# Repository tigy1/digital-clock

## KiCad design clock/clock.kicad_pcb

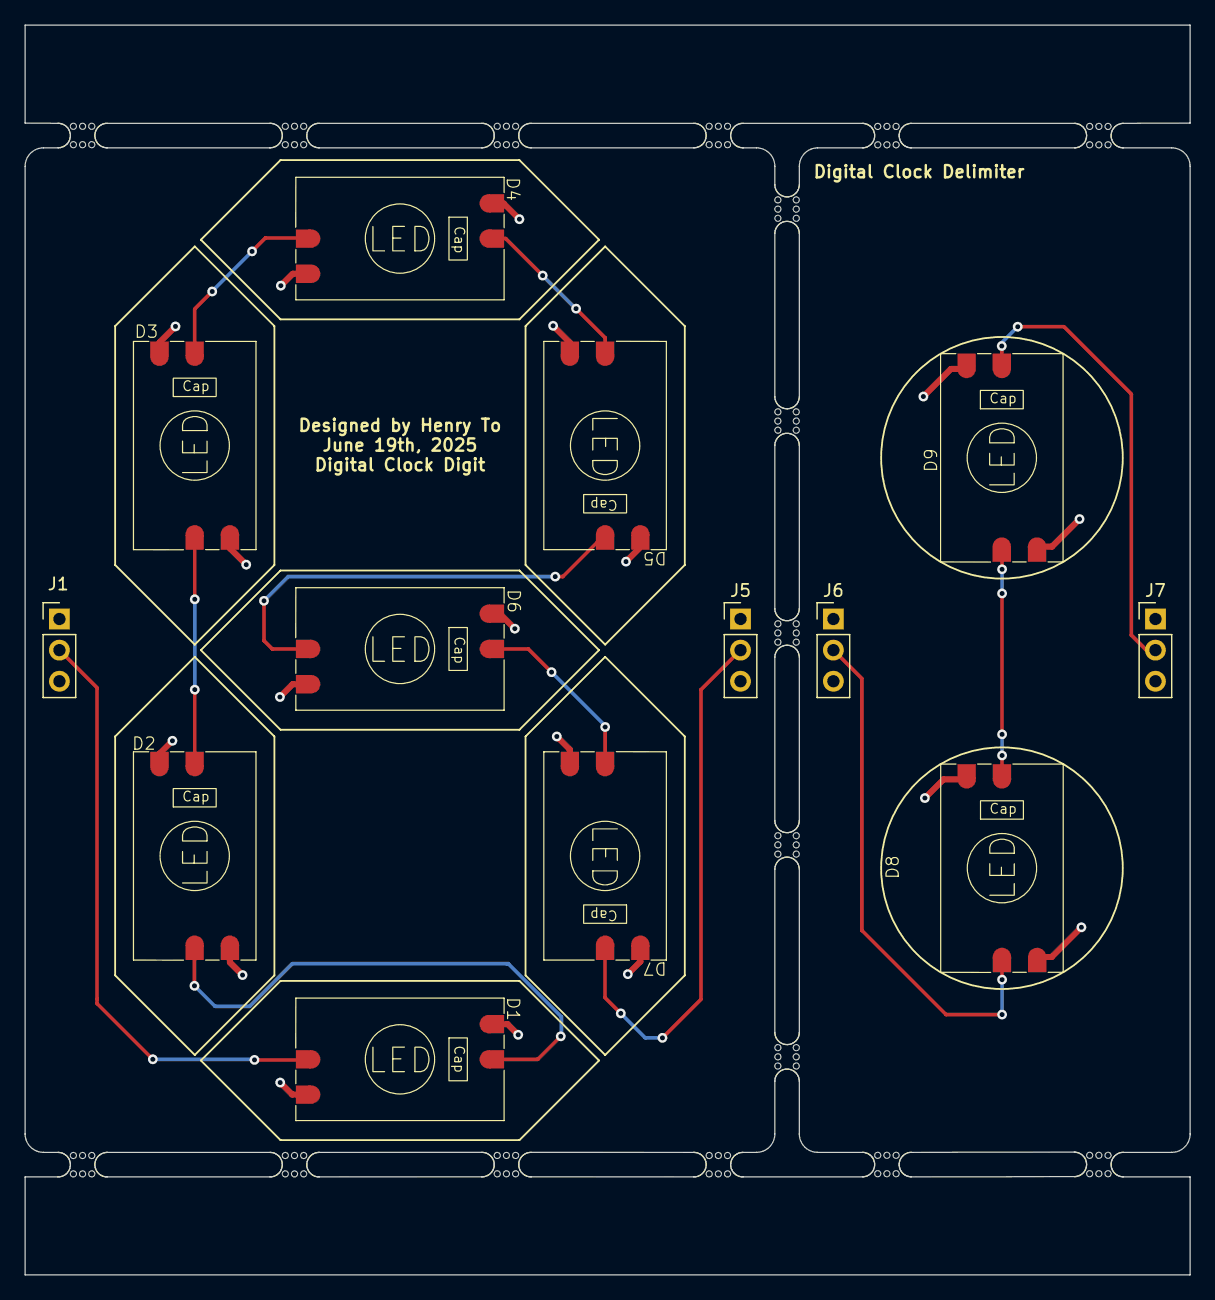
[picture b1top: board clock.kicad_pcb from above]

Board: 4 copper layers, 95.1 x 102.0 mm, 30 parts (0 on the bottom side), 14 nets.

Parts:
D1, D2, D3, D4, D5, D6, D7, D8, D9: WS2812B; oneLED
J1, J5, J6, J7: LED_connector; PinHeader_1x03_P2.54mm_Vertical
mouse-bite-2mm-slot, mouse-bite-2mm-slot1, mouse-bite-2mm-slot2, mouse-bite-2mm-slot3, mouse-bite-2mm-slot3#2, mouse-bite-2mm-slot3#3, mouse-bite-2mm-slot4, mouse-bite-2mm-slot5, mouse-bite-2mm-slot6, mouse-bite-2mm-slot7, mouse-bite-2mm-slot8, mouse-bite-2mm-slot9, mouse-bite-2mm-slot10, mouse-bite-2mm-slot11, mouse-bite-2mm-slot12, mouse-bite-2mm-slot13, mouse-bite-2mm-slot14: VAL**; mouse-bite-2mm-slot

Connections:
5V: D1.1 (VDD), D2.1 (VDD), D3.1 (VDD), D4.1 (VDD), D5.1 (VDD), D6.1 (VDD), D7.1 (VDD), J1.3, J5.3
5V2: D8.1 (VDD), D9.1 (VDD), J6.3, J7.3
D_In1: D1.4 (DIN), J1.2
D_In2: D8.4 (DIN), J6.2
D_Out1: D7.2 (DOUT), J5.2
D_Out2: D9.2 (DOUT), J7.2
GND: D1.3 (VSS), D2.3 (VSS), D3.3 (VSS), D4.3 (VSS), D5.3 (VSS), D6.3 (VSS), D7.3 (VSS), D8.3 (VSS), D9.3 (VSS), J1.1, J5.1, J6.1, J7.1
unnamed: D1.2 (DOUT), D2.4 (DIN)
unnamed: D2.2 (DOUT), D3.4 (DIN)
unnamed: D3.2 (DOUT), D4.4 (DIN)
unnamed: D4.2 (DOUT), D5.4 (DIN)
unnamed: D5.2 (DOUT), D6.4 (DIN)
unnamed: D6.2 (DOUT), D7.4 (DIN)
unnamed: D8.2 (DOUT), D9.4 (DIN)

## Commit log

2025-05-28 Added current KiCad files, almost finished LED schematic, microcontroller board & PCB design in progress
2025-05-28 Initialized stm32 code w/ stm32f103c6tx microcontroller
2025-05-30 Setup settings (UART, TIM2 timer, clock, & DMA) for microcontroller
2025-06-06 Wrote initialization functiosn for sending data to LED
    + basic preset functions for clearing all LEDS or setting all white
2025-06-06 committed changes of what previous commit message said
2025-06-06 Fixed bug where I used wrong MCU, replaced MCU & made new project file
2025-06-06 Added data sent flag and fixed up functions (dma_send & set functions)
2025-06-19 finished LED digit PCB, added gerber files, moved microcontroller kicad pcb files to different directory
2025-06-23 initialized i2c settings w/ microcontroller for ds3231
2025-06-23 prev message*
2025-06-25 created functions for ds3231 usage
    functions:
    - DS3231 register time initialization
    - Display current ds3231 time as digital leds
    - DS3231 i2c parsing
    - Decimal to DS3231 BCD conversion and vice versa
    *Also fixed function error by writing all function declarations
2025-06-26 Optimized code for size & tested code works
    - Code flash too large (>32k bits so did -Os optimization)
    - Digital clock led display based on Ds3231 works
    To Do: Make it so that digital clock is updated every minute
2025-06-26 Partially setup bday alarm & added EXTI pins
    To Do:
    - Try to organize all the time into a struct
    - Call digital clock setup in while loop
    - Finish alarm LED pattern functionality
2025-06-27 Added bug fixes and new changes
    - Organized time in struct for minimal calls to register in multiple
    spots
    - Finished digital clock call in while loop
    - Added colon blinking
    To Do:
    - Keep working on alarm functionality
2025-06-28 Separated LED & RGB function logic & cleaned code
2025-06-29 Added rainbow LED functionality and removed LED struct,added toggle struct
2025-07-11 added fastapi libraries & requirements list for it
2025-07-15 Finished code for DHT11 setup working with celsius
    Reorganized code into their own sections
    Got rid of AM/PM functionality, changed to military time
2025-08-05 added backend that makes external api calls to timezonedb,nws,&nominatim. uses fastapi to make the api and httpx to call external apis.
2025-08-06 Fixed bug for dht11 by creating timeout for while loop within dht11_read
2025-08-07 added new file for tkinter UI
2025-08-08 api functionality and tkinter progress -> added color schemes, frames, location input, and beginning tabview for clock/time switching
2025-08-08 finished general format of UI
2025-08-11 worked on weather tab UI adding visual aesthetics and buttons/display for temperature
2025-08-12 added celsius to fahrenheit function and finished ui for temp degree switching w/ button press delay and ui updates
2025-08-13 organized code by adding app_logic.py module for tkinter logic, partly completed clock tab displayon tkinter, added clock visual icon, WIP clock tab
2025-08-13 Finished UI for time tab, TODO: Call my fastAPI and connect to UI
2025-08-14 organized code by adding function in app_logic for delay and added functions (some w/ WIP code) fo r each button/switch widget
2025-08-15 fixed fastapi calls by adding email parameters to routes, started code on calling backend apis
2025-08-19 interfaced api calls to update data to time and weather in UI
2025-08-20 Organized api calls and code so that api data is called and saved when location is entered, not on tab presses. Added start of system where UX is updated every few minutes with time and weather updat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
2025-08-21 added error catching to incorrect location inputs and fixed api call refreshes so that there's onl y 1 existing refresh (.after) at a time
2025-08-22 Added accurate time keeping with minutes updating based on the seconds that the api received at first. Fixed bug where time displayed was 1 minute ahead. TODO: Fix api async functions working as inte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
